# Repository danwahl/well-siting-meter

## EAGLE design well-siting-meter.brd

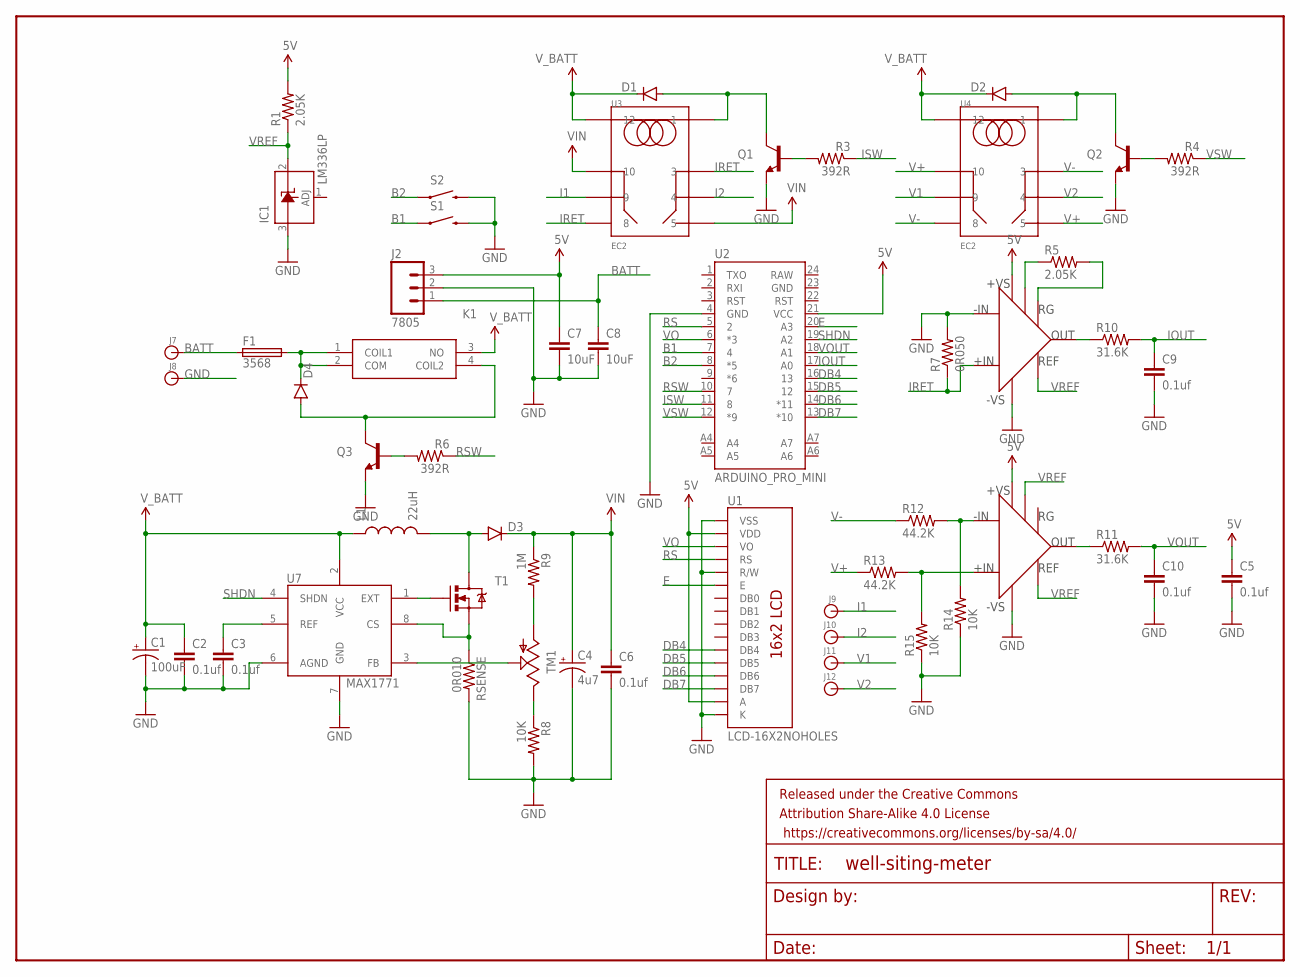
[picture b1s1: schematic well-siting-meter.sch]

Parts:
C1: 100uF; CPOL-RADIAL-1000UF-25V
C2, C3, C5, C6, C9, C10: 0.1uf; CAP-PTH-5MM
C4: 4u7; CPOL-RADIAL-1000UF-25V
C7, C8: 10uF; CAP-PTH-5MM
D1, D2, D3, D4: DIODEPTH; DIODE-1N4001
F1: 3568
FRAME1: FRAME-LETTER; CREATIVE_COMMONS
IC1: LM336LP; TO92
J2: 7805; 1X03
J7, J8, J9, J10, J11, J12: BANANA_CONN
K1: OJE-SH-105HM,000; OJ-SH-124LMH
L1: 22uH; 1415
Q1, Q2, Q3: TRANSISTOR_NPNTO92; TO-92
R1, R5: 2.05K; AXIAL-0.4
R3, R4, R6: 392R; AXIAL-0.4
R7: 0R050; AXIAL-0.6
R8, R14, R15: 10K; AXIAL-0.4
R9: 1M; AXIAL-0.4
R10, R11: 31.6K; AXIAL-0.4
R12, R13: 44.2K; AXIAL-0.4
RSENSE: 0R010; AXIAL-0.6
S1, S2: SWITCH-MOMENTARY-2PTH; TACTILE-PTH
T1: MOSFET-NCHANNELFQP30N06L; TO220V
TM1: TRIM3386; TRIM-3386
U1: LCD-16X2NOHOLES; LCD-16X2_NOHOLES
U2: ARDUINO_PRO_MINI
U3, U4: EC2
U5: AD623; DIP08
U6: AD629; DIP08
U7: MAX1771; DIP-08

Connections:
5V: C5.1, C7.1, J2.3, R1.P$2 (2), U1.2 (VDD), U1.15 (A), U2.21 (VCC), U5.7 (+VS), U6.7 (+VS)
B1: S1.1, U2.7 (4)
B2: S2.1, U2.8 (*5)
BATT: C8.1, F1.1, F1.2 (1), J2.1, J7.P$1
DB4: U1.11 (DB4), U2.16 (13)
DB5: U1.12 (DB5), U2.15 (12)
DB6: U1.13 (DB6), U2.14 (*11)
DB7: U1.14 (DB7), U2.13 (*10)
E: U1.6 (E), U2.20 (A3)
FUSE: D4.C, F1.3 (2), F1.4 (2), K1.1 (COIL1), K1.2 (COM)
GND: C1.2 (-), C2.2, C3.2, C4.2 (-), C5.2, C6.2, C7.2, C8.2, C9.2, C10.2, IC1.3 (A), J2.2, J8.P$1, Q1.1 (E), Q2.1 (E), Q3.1 (E), R7.P$2 (2), R8.P$2 (2), R14.P$1 (1), R15.P$1 (1), RSENSE.P$2 (2), S1.3 (2), S2.3 (2), U1.1 (VSS), U1.5 (R/W), U1.16 (K), U2.4 (GND), U5.2 (-IN), U5.4 (-VS), U6.4 (-VS), U7.6 (AGND), U7.7 (GND)
I1: J9.P$1, U3.9
I2: J10.P$1, U3.4
IOUT: C9.1, R10.P$2 (2), U2.17 (A0)
IRET: R7.P$1 (1), U3.3, U3.8, U5.3 (+IN)
ISW: R3.P$1 (1), U2.11 (8)
unnamed: D2.A, Q2.3 (C), U4.1
unnamed: Q2.2 (B), R4.P$2 (2)
unnamed: D1.A, Q1.3 (C), U3.1
unnamed: Q1.2 (B), R3.P$2 (2)
unnamed: R9.P$2 (2), TM1.3 (A)
unnamed: C3.1, U7.5 (REF)
unnamed: R8.P$1 (1), TM1.1 (E)
unnamed: D3.A, L1.P2 (2), T1.2 (D)
unnamed: T1.1 (G), U7.1 (EXT)
unnamed: RSENSE.P$1 (1), T1.3 (S), U7.8 (CS)
unnamed: R10.P$1 (1), U5.6 (OUT)
unnamed: R12.P$2 (2), R14.P$2 (2), U6.2 (-IN)
unnamed: R11.P$1 (1), U6.6 (OUT)
unnamed: TM1.2 (S), U7.3 (FB)
unnamed: R13.P$2 (2), R15.P$2 (2), U6.3 (+IN)
unnamed: D4.A, K1.4 (COIL2), Q3.3 (C)
unnamed: Q3.2 (B), R6.P$2 (2)
unnamed: R5.P$1 (1), U5.1 (-RG)
unnamed: R5.P$2 (2), U5.8 (+RG)
RS: U1.4 (RS), U2.5 (2)
RSW: R6.P$1 (1), U2.10 (7)
SHDN: U2.19 (A2), U7.4 (SHDN)
V1: J11.P$1, U4.9
V2: J12.P$1, U4.4
V+: R13.P$1 (1), U4.5, U4.10
V-: R12.P$1 (1), U4.3, U4.8
VIN: C4.1 (+), C6.1, D3.C, R9.P$1 (1), U3.5, U3.10
VO: U1.3 (VO), U2.6 (*3)
VOUT: C10.1, R11.P$2 (2), U2.18 (A1)
VREF: IC1.2 (C), R1.P$1 (1), U5.5 (REF), U6.1 (-RG), U6.5 (REF)
VSW: R4.P$1 (1), U2.12 (*9)
V_BATT: C1.1 (+), C2.1, D1.C, D2.C, K1.3 (NO), L1.P1 (1), U3.12, U4.12, U7.2 (VCC)

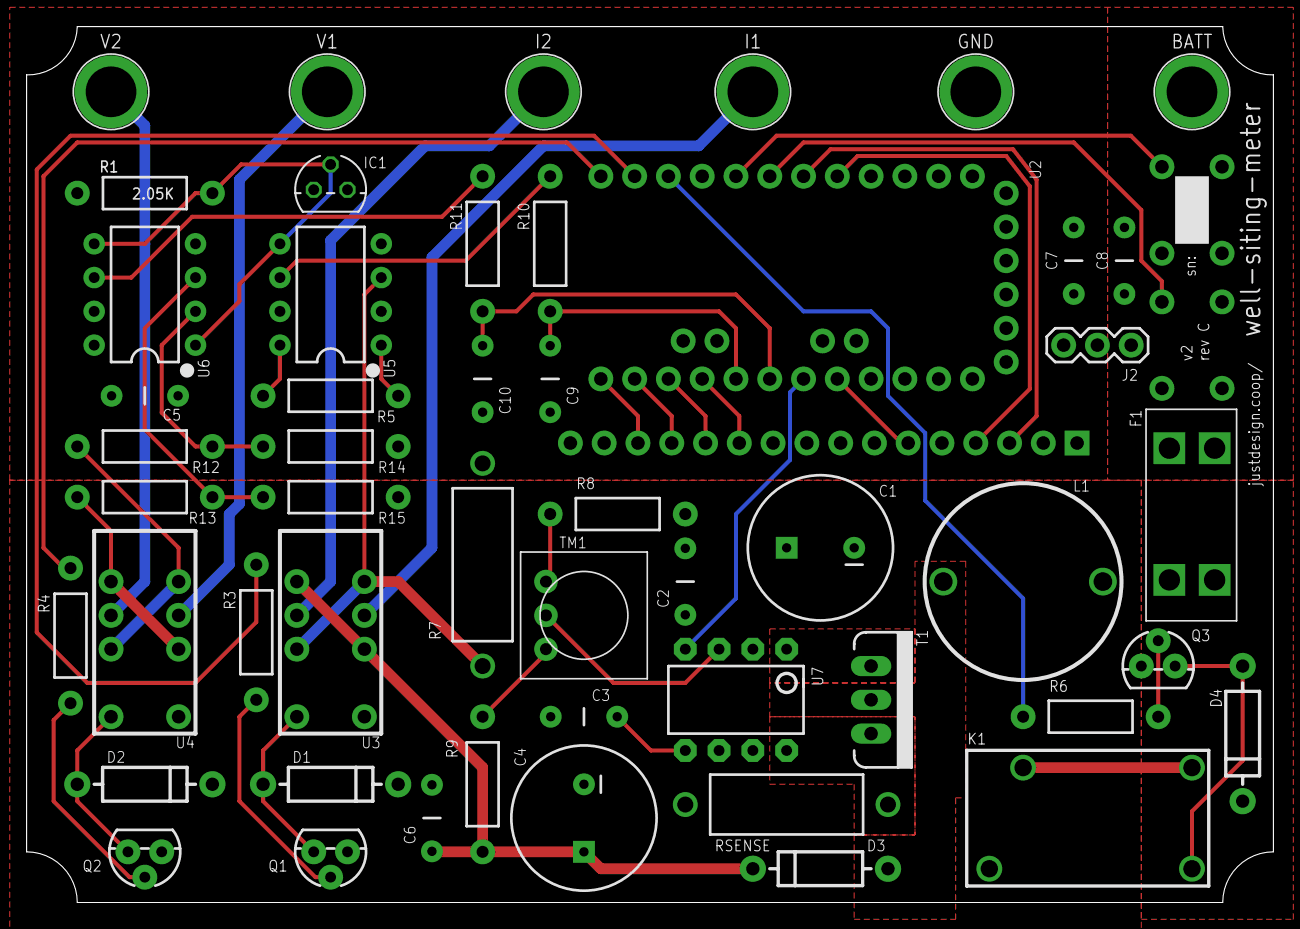
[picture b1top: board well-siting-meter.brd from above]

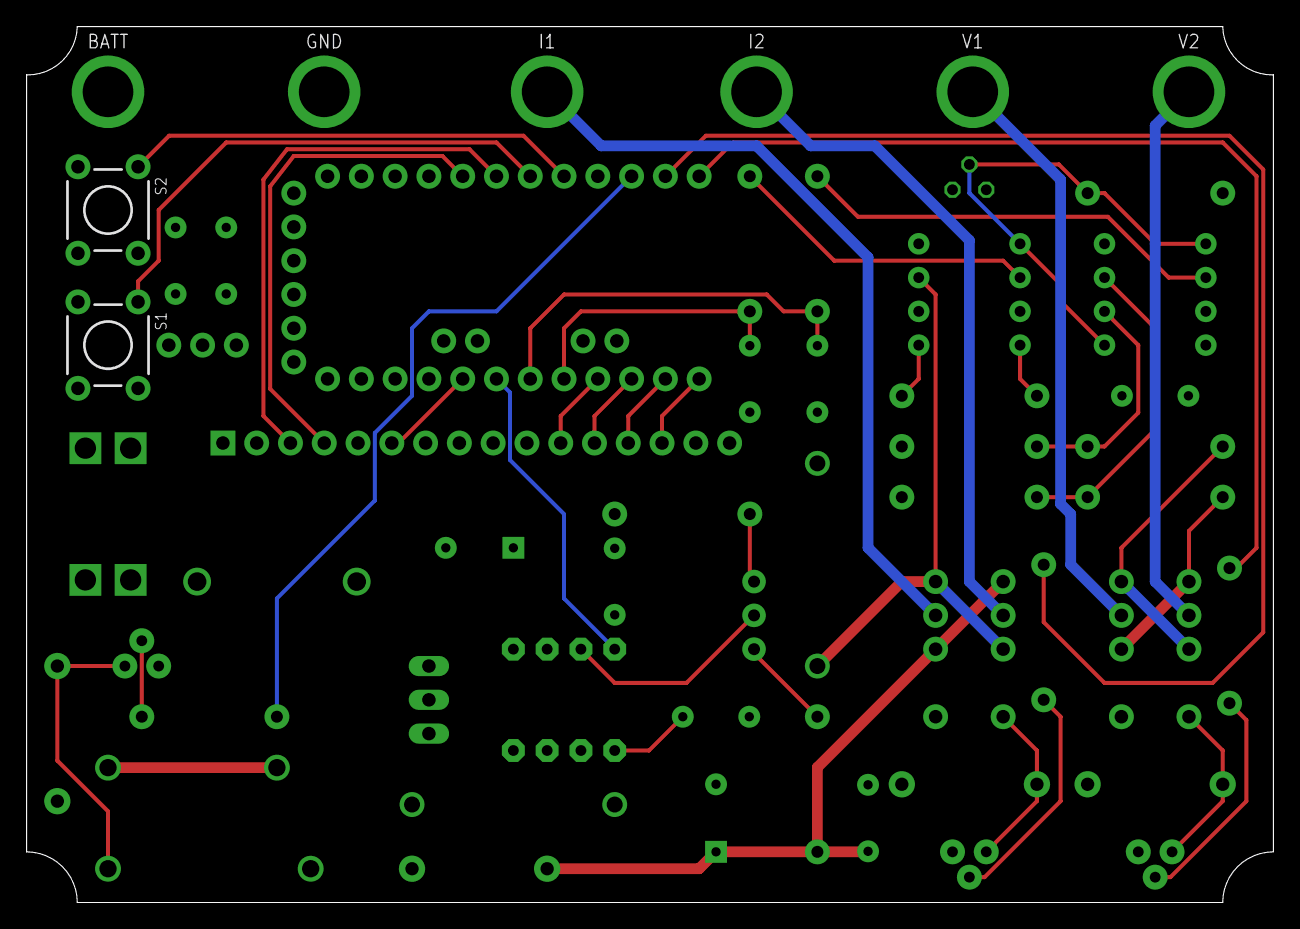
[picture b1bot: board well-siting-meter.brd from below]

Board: 2 copper layers, 93.8 x 65.9 mm, 55 parts (3 on the bottom side), 48 nets.

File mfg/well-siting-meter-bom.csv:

"Qty";"Value";"Device";"Package";"Parts";"Description";"PN";"PN2";"PROD_ID";
"3";"";"BANANA_CONN";"BANANA_CONN";"J7, J9, J11";"Through-hole banana jack";"1568-1664-ND";"";"";
"3";"";"BANANA_CONN";"BANANA_CONN";"J8, J10, J12";"Through-hole banana jack";"1568-1665-ND";"";"";
"2";"";"DIODEPTH";"DIODE-1N4001";"D1, D2";"Diode";"1N4001-TPMSCT-ND";"";"";
"1";"";"DIODEPTH";"DIODE-1N4001";"D3";"Diode";"EGP20FCT-ND";"";"";
"2";"";"TRANSISTOR_NPNTO92";"TO-92";"Q1, Q2";"Generic NPN BJT";"PN2222AFS-ND";"";"";
"1";"";"TRIM3386";"TRIM-3386";"TM1";"";"1528-1997-ND ";"";"";
"1";"0.1uf";"CAPPTH1";"CAP-PTH-5MM";"C6";"Capacitor";"445-173449-1-ND";"";"";
"4";"0.1uf";"CAPPTH1";"CAP-PTH-5MM";"C2, C3, C9, C10";"Capacitor";"BC2665CT-ND";"";"";
"1";"0R010";"RESISTORPTH-1W";"AXIAL-0.6";"RSENSE";"Resistor";"696-1729-ND";"";"";
"1";"0R050";"RESISTORPTH-1W";"AXIAL-0.6";"R7";"Resistor";"696-1731-ND";"";"";
"1";"100K";"RESISTORPTH-1/4W";"AXIAL-0.4";"R6";"Resistor";"100KXBK-ND";"";"";
"1";"100uF";"CAP_POLPTH4";"CPOL-RADIAL-1000UF-25V";"C1";"Capacitor Polarized";"1572-1306-ND";"";"";
"3";"10K";"RESISTORPTH-1/4W";"AXIAL-0.4";"R1, R2, R8";"Resistor";"10.0KXBK-ND";"";"";
"2";"10uF";"CAPPTH1";"CAP-PTH-5MM";"C7, C8";"Capacitor";"445-173437-1-ND";"";"";
"1";"1M";"RESISTORPTH-1/4W";"AXIAL-0.4";"R9";"Resistor";"1.00MXBK-ND";"";"";
"1";"2.05K";"RESISTORPTH-1/4W";"AXIAL-0.4";"R5";"Resistor";"2.05KXBK-ND";"";"";
"1";"22uH";"WE-FAMI";"1415";"L1";"";"732-7163-ND";"";"";
"2";"31.6K";"RESISTORPTH-1/4W";"AXIAL-0.4";"R10, R11";"Resistor";"31.6KXBK-ND";"";"";
"2";"392R";"RESISTORPTH-1/4W";"AXIAL-0.4";"R3, R4";"Resistor";"392XBK-ND";"";"";
"1";"47uH";"MURATA1400";"MURATA1400";"L2";"";"811-2633-ND";"";"";
"1";"4u7";"CAP_POLPTH4";"CPOL-RADIAL-1000UF-25V";"C4";"Capacitor Polarized";"399-6091-ND";"";"";
"1";"7805";"M03PTH";"1X03";"J2";"Header 3";"811-2196-5-ND";"LM7805CT-ND";"";
"2";"AD623";"AD623";"DIP08";"U5, U6";"";"AD623ANZ-ND";"";"";
"1";"ARDUINO_PRO_MINI";"ARDUINO_PRO_MINI";"ARDUINO_PRO_MINI";"U2";"";"1568-1055-ND";"";"";
"2";"EC2";"EC2";"EC2";"U3, U4";"";"399-11029-5-ND";"";"";
"1";"FRAME-LETTER";"FRAME-LETTER";"CREATIVE_COMMONS";"FRAME1";"Schematic Frame";"";"";"";
"1";"LCD-16X2NOHOLES";"LCD-16X2NOHOLES";"LCD-16X2_NOHOLES";"U1";"Standard text-only 16x2 parallel input LCD";"1528-1502-ND";"";"";
"1";"MAX1771";"MAX1771";"DIP-08";"U7";"";"MAX1771CPA+-ND";"";"";
"1";"MOSFET-NCHANNELFQP30N06L";"MOSFET-NCHANNELFQP30N06L";"TO220V";"T1";"Common NMOSFET Parts";"FDP33N25-ND";"";"TRANS-10060";
"2";"SWITCH-MOMENTARY-2PTH";"SWITCH-MOMENTARY-2PTH";"TACTILE-PTH";"S1, S2";"Various NO switches- pushbuttons, reed, etc";"SW406-ND";"";" SWCH-08441";

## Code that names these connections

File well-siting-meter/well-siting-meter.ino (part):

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#define VO_PIN          3
#define B1_PIN          4
#define B2_PIN          5
#define RSW_PIN         7
#define ISW_PIN         8
#define VSW_PIN         9
#define DB7_PIN         10
#define DB6_PIN         11
#define DB5_PIN         12
#define DB4_PIN         13
#define IOUT_PIN        A0
#define VOUT_PIN        A1
#define SHDN_PIN        A2
#define EN_PIN          A3

// other variables
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  pinMode(B2_PIN, INPUT_PULLUP);

  // setup switches
  pinMode(RSW_PIN, OUTPUT);
  pinMode(ISW_PIN, OUTPUT);
  pinMode(VSW_PIN, OUTPUT);

  // setup boost shutdown
  pinMode(SHDN_PIN, OUTPUT);

  // setup analoginputs
  pinMode(IOUT_PIN, INPUT);
  pinMode(VOUT_PIN, INPUT);

  // reset pin states
  reset(INIT);
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      lcd.print("|###           |");

      // enable rsw
      digitalWrite(RSW_PIN, HIGH);

      // wait for relay to enable
      if(wait(B2_PIN, RELAY_TIMEOUT) <= 0) {
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      lcd.print("|##############|");

      // disable rsw
      digitalWrite(RSW_PIN, LOW);

      // wait and transition
      wait(0, STOP_TIMEOUT);
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      lcd.print(iout);

      // disable rsw
      digitalWrite(RSW_PIN, LOW);

      // wait for relay to enable
      if(wait(B2_PIN, RELAY_TIMEOUT) <= 0) {
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  static int n = NUM_MEAS*2;
  
  // check dir
  if(digitalRead(ISW_PIN) != dir) {
    digitalWrite(ISW_PIN, dir);

#ifdef DEBUG
    Serial.println(String("isw = ") + dir);
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  
  if(boost == ON) {
    // enable boost
    digitalWrite(SHDN_PIN, LOW);

#ifdef DEBUG
    Serial.println("boost = ON");
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  float imeas[n];

  // setup fwd
  if(digitalRead(VSW_PIN) != FWD) {
    digitalWrite(VSW_PIN, FWD);

#ifdef DEBUG
    Serial.println("vsw = FWD");
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  // fwd meas
  for(int i = 0; i < NUM_MEAS; i++) {
    // read and convert
    analogRead(VOUT_PIN);
    if(wait(B2_PIN, MEAS_TIMEOUT) <= 0) {
      return 0;
    }
    vfmeas[i] = convert(VOUT_PIN, V_GAIN);


    // read and convert
    analogRead(IOUT_PIN);
    if(wait(B2_PIN, MEAS_TIMEOUT) <= 0) {
      return 0;
    }
    imeas[i] = convert(IOUT_PIN, I_GAIN)/R_SENSE;

#ifdef DEBUG
    Serial.println(String("") + i + ": vfmeas = " + vfmeas[i] + ", imeas = " + imeas[i]);
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  }

  // setup rev
  digitalWrite(VSW_PIN, REV);

#ifdef DEBUG
    Serial.println("vsw = REV");
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  // rev meas
  for(int i = 0; i < NUM_MEAS; i++) {
    // read and convert
    analogRead(VOUT_PIN);
    if(wait(B2_PIN, MEAS_TIMEOUT) <= 0) {
      return 0;
    }
    vrmeas[i] = convert(VOUT_PIN, V_GAIN);


    // read and convert
    analogRead(IOUT_PIN);
    if(wait(B2_PIN, MEAS_TIMEOUT) <= 0) {
      return 0;
    }
    imeas[i + NUM_MEAS] = convert(IOUT_PIN, I_GAIN)/R_SENSE;

#ifdef DEBUG
    Serial.println(String("") + i + ": vrmeas = " + vrmeas[i] + ", imeas = " + imeas[i + NUM_MEAS]);
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
  if(boost == ON) {
    // disable boost
    digitalWrite(SHDN_PIN, HIGH);

#ifdef DEBUG
    Serial.println("boost = OFF");
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  Serial.println(String("reset(") + next + ")");
#endif

  digitalWrite(SHDN_PIN, HIGH);
  digitalWrite(RSW_PIN, LOW);
  digitalWrite(ISW_PIN, FWD);
  digitalWrite(VSW_PIN, FWD);

  vgnd = 0;
  vfwd = 0;
  vrev = 0;
  ifwd = 0;
  irev = 0;
  vout = 0;
  iout = 0;
  
  state = next;
}
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
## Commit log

2017-06-04 initial commit (schematic)
2018-04-14 boost circuit, lcd screen, starting board layout
2018-04-15 "finished" design, but need to update boot circuity for > 10W max
2018-04-15 added boost circuit
2018-04-15 adding part numbers
2018-04-16 updated inductor, adding part numbers
2018-04-16 fixed board outline, added remaining part numbers
2018-04-16 rearranged a few polygons
2018-04-17 prep for mfg
2018-04-17 adding optional 2nd inductor, more mfg prep
2018-04-17 rev - mfg files
2018-04-23 fixed cap packages (5mm)
2018-04-27 adding arduino project, starting rev A fixes
2018-04-29 updating arduino code
2018-05-02 rev A updates, arduino testing
2018-05-02 rev A, bom updates
2018-05-06 rev A manufacturing
2018-05-11 screen setup
2018-05-11 instrumenting code for debug
2018-05-11 debug implementation for testing
2018-06-11 start of rev B updates (added relay, AD629, fuse)
2018-06-30 rev B updates (AD629, fuse holder, power relay)
2018-06-30 adding ic1 for 2.5 vref
2018-07-02 rev B build
2018-08-05 updated arduino code for rsw
2018-08-06 rev C initial commit, modifying vref and voltage input resistors

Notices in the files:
parts and their libraries:
SparkFun-Boards: Licensing: Creative Commons ShareAlike 4.0 International - https://creativecommons.org/licenses/by-sa/4.0
SparkFun-Aesthetics: Released under the Creative Commons Attribution Share-Alike 4.0 License
SparkFun-Aesthetics: https://creativecommons.org/licenses/by-sa/4.0
